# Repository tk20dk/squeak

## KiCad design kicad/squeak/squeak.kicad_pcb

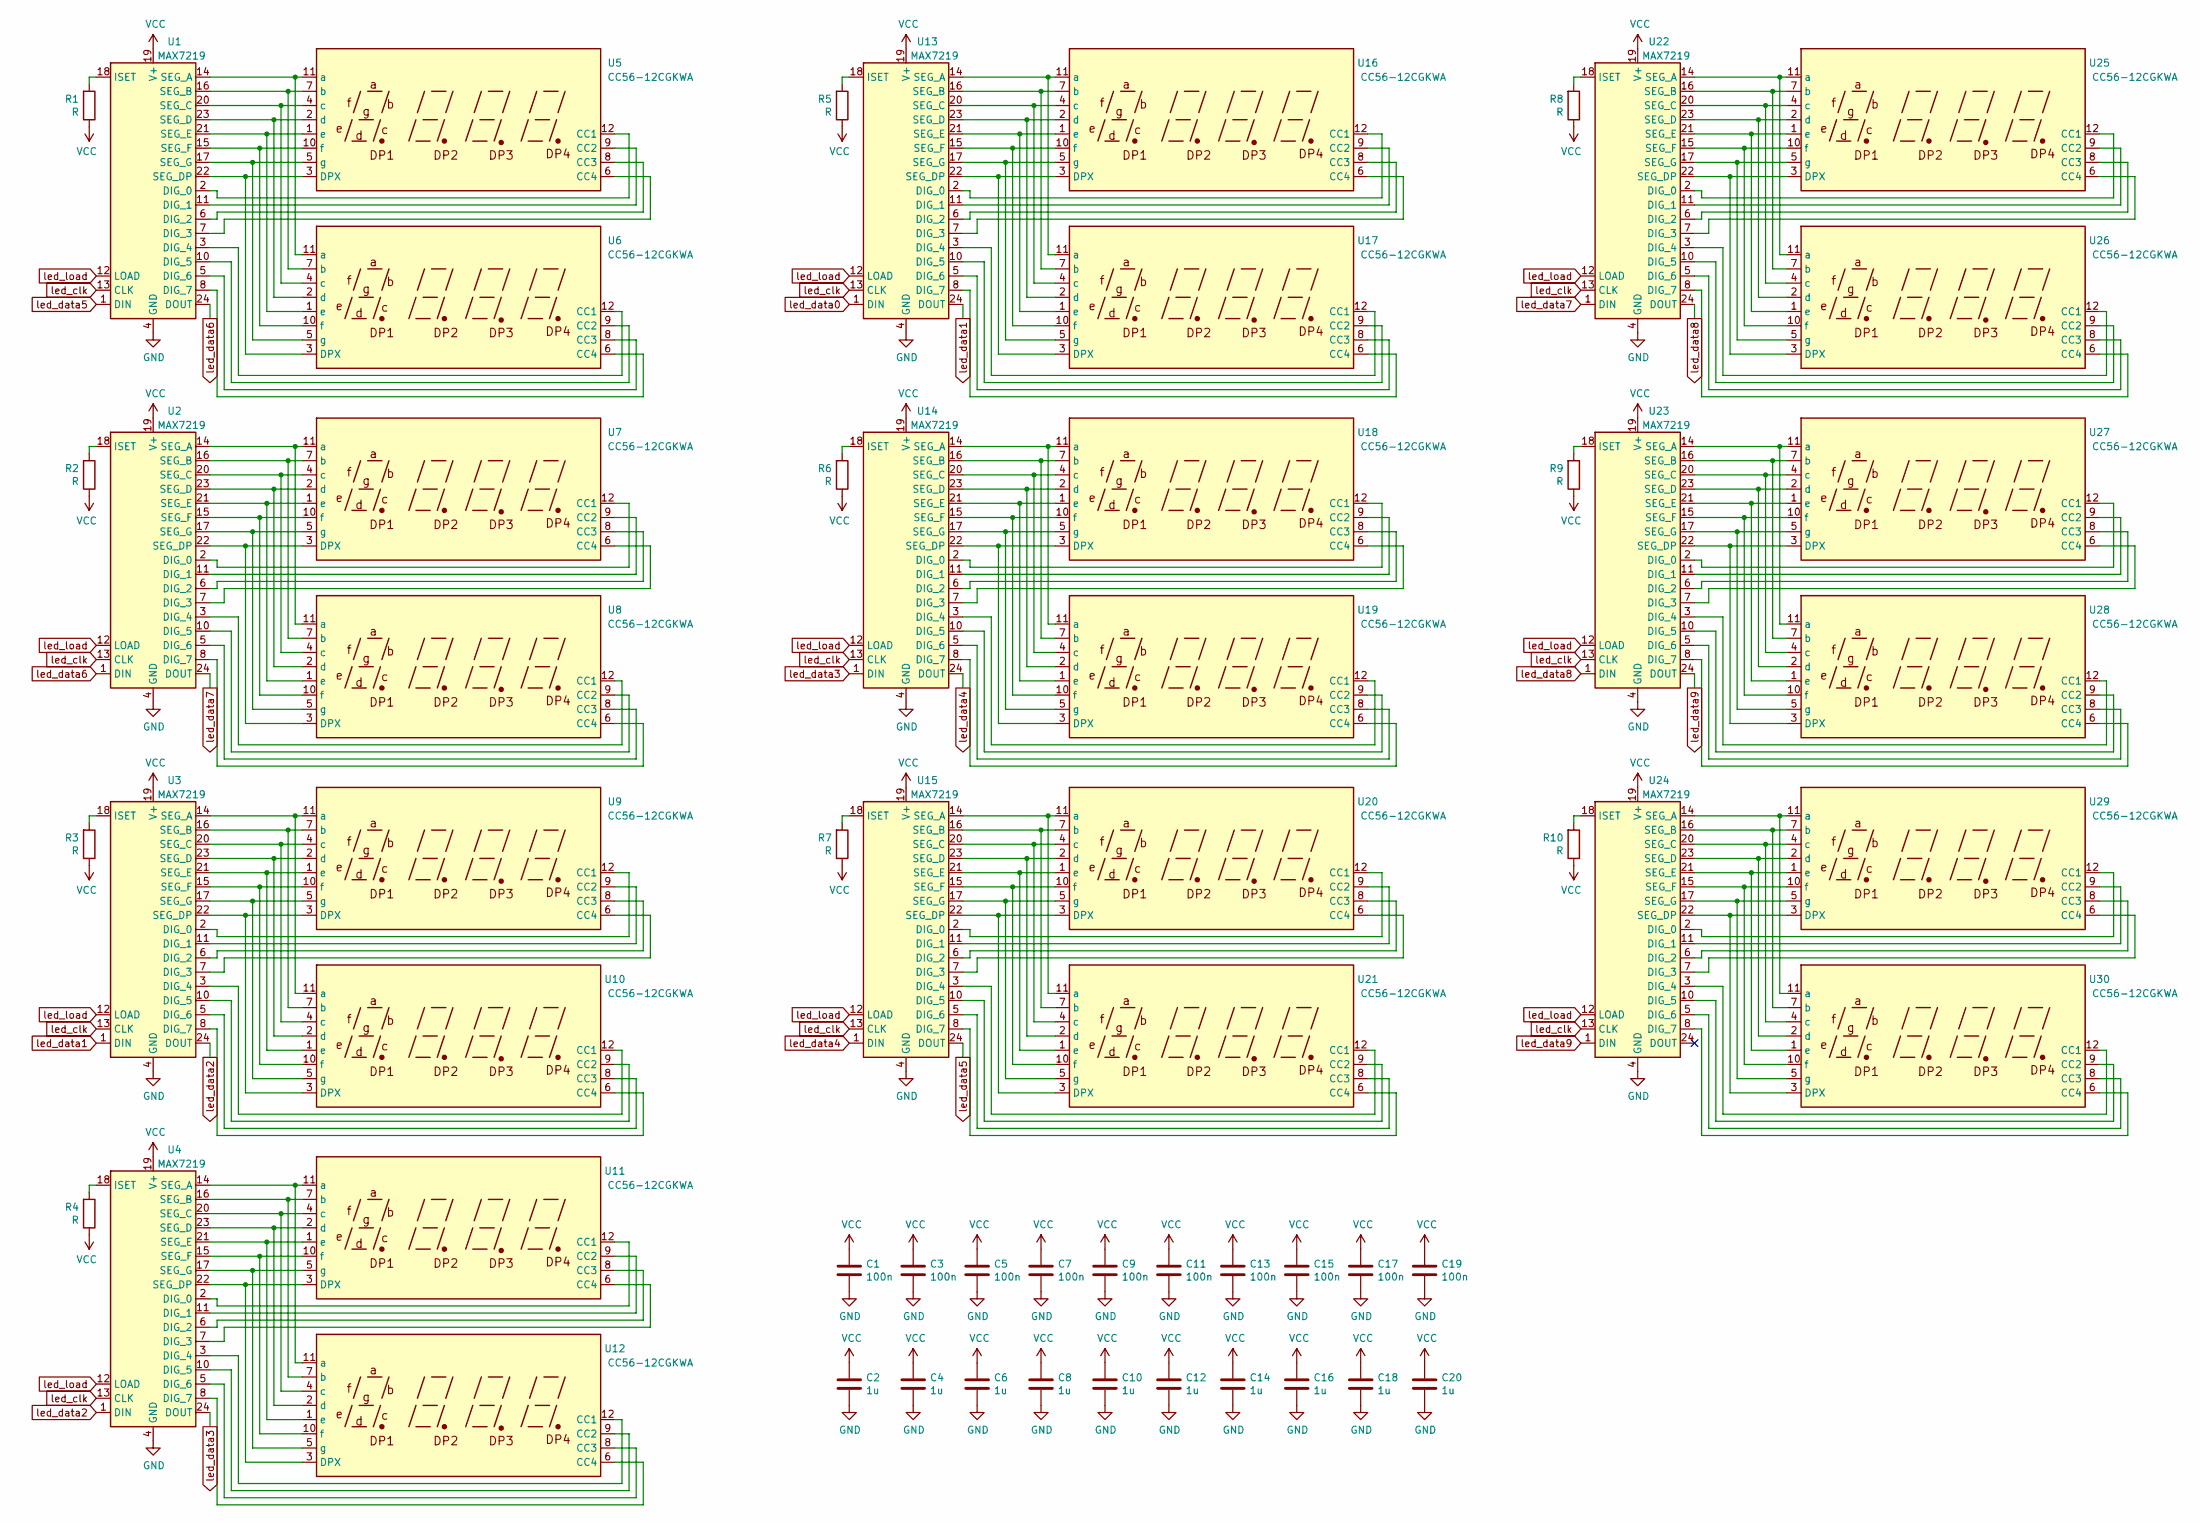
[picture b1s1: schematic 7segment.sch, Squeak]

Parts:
C1, C3, C5, C7, C9, C11, C13, C15, C17, C19: 100n; C_0603_1608Metric
C2, C4, C6, C8, C10, C12, C14, C16, C18, C20: 1u; C_0805_2012Metric
R1, R2, R3, R4, R5, R6, R7, R8, R9, R10: R; R_0603_1608Metric
U1, U2, U3, U4, U13, U14, U15, U22, U23, U24: MAX7219; SOIC-24W_7.5x15.4mm_P1.27mm
U5, U6, U7, U8, U9, U10, U11, U12, U16, U17, U18, U19, U20, U21, U25, U26, U27, U28, U29, U30: CC56-12CGKWA; CA56-12CGKWA

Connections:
GND: C1.2, C2.2, C3.2, C4.2, C5.2, C6.2, C7.2, C8.2, C9.2, C10.2, C11.2, C12.2, C13.2, C14.2, C15.2, C16.2, C17.2, C18.2, C19.2, C20.2, U1.4 (GND), U1.9 (GND), U2.4 (GND), U2.9 (GND), U3.4 (GND), U3.9 (GND), U4.4 (GND), U4.9 (GND), U13.4 (GND), U13.9 (GND), U14.4 (GND), U14.9 (GND), U15.4 (GND), U15.9 (GND), U22.4 (GND), U22.9 (GND), U23.4 (GND), U23.9 (GND), U24.4 (GND), U24.9 (GND); also elsewhere on the board
unnamed: R1.2, U1.18 (ISET)
unnamed: R2.2, U2.18 (ISET)
unnamed: R3.2, U3.18 (ISET)
unnamed: R4.2, U4.18 (ISET)
unnamed: R5.2, U13.18 (ISET)
unnamed: R6.2, U14.18 (ISET)
unnamed: R7.2, U15.18 (ISET)
unnamed: R8.2, U22.18 (ISET)
unnamed: R9.2, U23.18 (ISET)
unnamed: R10.2, U24.18 (ISET)
unnamed: U1.2 (DIG_0), U5.12 (CC1)
unnamed: U1.3 (DIG_4), U6.12 (CC1)
unnamed: U1.5 (DIG_6), U6.8 (CC3)
unnamed: U1.6 (DIG_2), U5.8 (CC3)
unnamed: U1.7 (DIG_3), U5.6 (CC4)
unnamed: U1.8 (DIG_7), U6.6 (CC4)
unnamed: U1.10 (DIG_5), U6.9 (CC2)
unnamed: U1.11 (DIG_1), U5.9 (CC2)
unnamed: U1.14 (SEG_A), U5.11 (a), U6.11 (a)
unnamed: U1.15 (SEG_F), U5.10 (f), U6.10 (f)
unnamed: U1.16 (SEG_B), U5.7 (b), U6.7 (b)
unnamed: U1.17 (SEG_G), U5.5 (g), U6.5 (g)
unnamed: U1.20 (SEG_C), U5.4 (c), U6.4 (c)
unnamed: U1.21 (SEG_E), U5.1 (e), U6.1 (e)
unnamed: U1.22 (SEG_DP), U5.3 (DPX), U6.3 (DPX)
unnamed: U1.23 (SEG_D), U5.2 (d), U6.2 (d)
unnamed: U2.2 (DIG_0), U7.12 (CC1)
unnamed: U2.3 (DIG_4), U8.12 (CC1)
unnamed: U2.5 (DIG_6), U8.8 (CC3)
unnamed: U2.6 (DIG_2), U7.8 (CC3)
unnamed: U2.7 (DIG_3), U7.6 (CC4)
unnamed: U2.8 (DIG_7), U8.6 (CC4)
unnamed: U2.10 (DIG_5), U8.9 (CC2)
unnamed: U2.11 (DIG_1), U7.9 (CC2)
unnamed: U2.14 (SEG_A), U7.11 (a), U8.11 (a)
unnamed: U2.15 (SEG_F), U7.10 (f), U8.10 (f)
unnamed: U2.16 (SEG_B), U7.7 (b), U8.7 (b)
unnamed: U2.17 (SEG_G), U7.5 (g), U8.5 (g)
unnamed: U2.20 (SEG_C), U7.4 (c), U8.4 (c)
unnamed: U2.21 (SEG_E), U7.1 (e), U8.1 (e)
unnamed: U2.22 (SEG_DP), U7.3 (DPX), U8.3 (DPX)
unnamed: U2.23 (SEG_D), U7.2 (d), U8.2 (d)
unnamed: U3.2 (DIG_0), U9.12 (CC1)
unnamed: U3.6 (DIG_2), U9.8 (CC3)
unnamed: U3.7 (DIG_3), U9.6 (CC4)
unnamed: U3.11 (DIG_1), U9.9 (CC2)
unnamed: U3.21 (SEG_E), U9.1 (e), U10.1 (e)
unnamed: U3.23 (SEG_D), U9.2 (d), U10.2 (d)
unnamed: U3.22 (SEG_DP), U9.3 (DPX), U10.3 (DPX)
unnamed: U3.20 (SEG_C), U9.4 (c), U10.4 (c)
unnamed: U3.17 (SEG_G), U9.5 (g), U10.5 (g)
unnamed: U3.8 (DIG_7), U10.6 (CC4)
unnamed: U3.16 (SEG_B), U9.7 (b), U10.7 (b)
unnamed: U3.5 (DIG_6), U10.8 (CC3)
unnamed: U3.10 (DIG_5), U10.9 (CC2)
unnamed: U3.15 (SEG_F), U9.10 (f), U10.10 (f)
unnamed: U3.14 (SEG_A), U9.11 (a), U10.11 (a)
unnamed: U3.3 (DIG_4), U10.12 (CC1)
unnamed: U4.21 (SEG_E), U11.1 (e), U12.1 (e)
unnamed: U4.23 (SEG_D), U11.2 (d), U12.2 (d)
unnamed: U4.22 (SEG_DP), U11.3 (DPX), U12.3 (DPX)
unnamed: U4.20 (SEG_C), U11.4 (c), U12.4 (c)
unnamed: U4.17 (SEG_G), U11.5 (g), U12.5 (g)
unnamed: U4.7 (DIG_3), U11.6 (CC4)
unnamed: U4.16 (SEG_B), U11.7 (b), U12.7 (b)
unnamed: U4.6 (DIG_2), U11.8 (CC3)
unnamed: U4.11 (DIG_1), U11.9 (CC2)
unnamed: U4.15 (SEG_F), U11.10 (f), U12.10 (f)
unnamed: U4.14 (SEG_A), U11.11 (a), U12.11 (a)
unnamed: U4.2 (DIG_0), U11.12 (CC1)
unnamed: U4.8 (DIG_7), U12.6 (CC4)
unnamed: U4.5 (DIG_6), U12.8 (CC3)
unnamed: U4.10 (DIG_5), U12.9 (CC2)
unnamed: U4.3 (DIG_4), U12.12 (CC1)
unnamed: U13.2 (DIG_0), U16.12 (CC1)
unnamed: U13.3 (DIG_4), U17.12 (CC1)
unnamed: U13.5 (DIG_6), U17.8 (CC3)
unnamed: U13.6 (DIG_2), U16.8 (CC3)
unnamed: U13.7 (DIG_3), U16.6 (CC4)
unnamed: U13.8 (DIG_7), U17.6 (CC4)
unnamed: U13.10 (DIG_5), U17.9 (CC2)
unnamed: U13.11 (DIG_1), U16.9 (CC2)
unnamed: U13.14 (SEG_A), U16.11 (a), U17.11 (a)
unnamed: U13.15 (SEG_F), U16.10 (f), U17.10 (f)
unnamed: U13.16 (SEG_B), U16.7 (b), U17.7 (b)
unnamed: U13.17 (SEG_G), U16.5 (g), U17.5 (g)
unnamed: U13.20 (SEG_C), U16.4 (c), U17.4 (c)
unnamed: U13.21 (SEG_E), U16.1 (e), U17.1 (e)
unnamed: U13.22 (SEG_DP), U16.3 (DPX), U17.3 (DPX)
unnamed: U13.23 (SEG_D), U16.2 (d), U17.2 (d)
unnamed: U14.2 (DIG_0), U18.12 (CC1)
unnamed: U14.3 (DIG_4), U19.12 (CC1)
unnamed: U14.5 (DIG_6), U19.8 (CC3)
unnamed: U14.6 (DIG_2), U18.8 (CC3)
unnamed: U14.7 (DIG_3), U18.6 (CC4)
unnamed: U14.8 (DIG_7), U19.6 (CC4)
unnamed: U14.10 (DIG_5), U19.9 (CC2)
unnamed: U14.11 (DIG_1), U18.9 (CC2)
unnamed: U14.14 (SEG_A), U18.11 (a), U19.11 (a)
unnamed: U14.15 (SEG_F), U18.10 (f), U19.10 (f)
unnamed: U14.16 (SEG_B), U18.7 (b), U19.7 (b)
unnamed: U14.17 (SEG_G), U18.5 (g), U19.5 (g)
unnamed: U14.20 (SEG_C), U18.4 (c), U19.4 (c)
unnamed: U14.21 (SEG_E), U18.1 (e), U19.1 (e)
unnamed: U14.22 (SEG_DP), U18.3 (DPX), U19.3 (DPX)
unnamed: U14.23 (SEG_D), U18.2 (d), U19.2 (d)
unnamed: U15.2 (DIG_0), U20.12 (CC1)
unnamed: U15.3 (DIG_4), U21.12 (CC1)
unnamed: U15.5 (DIG_6), U21.8 (CC3)
unnamed: U15.6 (DIG_2), U20.8 (CC3)
unnamed: U15.7 (DIG_3), U20.6 (CC4)
unnamed: U15.8 (DIG_7), U21.6 (CC4)
unnamed: U15.10 (DIG_5), U21.9 (CC2)
unnamed: U15.11 (DIG_1), U20.9 (CC2)
unnamed: U15.14 (SEG_A), U20.11 (a), U21.11 (a)
unnamed: U15.15 (SEG_F), U20.10 (f), U21.10 (f)
unnamed: U15.16 (SEG_B), U20.7 (b), U21.7 (b)
unnamed: U15.17 (SEG_G), U20.5 (g), U21.5 (g)
unnamed: U15.20 (SEG_C), U20.4 (c), U21.4 (c)
unnamed: U15.21 (SEG_E), U20.1 (e), U21.1 (e)
unnamed: U15.22 (SEG_DP), U20.3 (DPX), U21.3 (DPX)
unnamed: U15.23 (SEG_D), U20.2 (d), U21.2 (d)
unnamed: U22.2 (DIG_0), U25.12 (CC1)
unnamed: U22.3 (DIG_4), U26.12 (CC1)
unnamed: U22.5 (DIG_6), U26.8 (CC3)
unnamed: U22.6 (DIG_2), U25.8 (CC3)
unnamed: U22.7 (DIG_3), U25.6 (CC4)
unnamed: U22.8 (DIG_7), U26.6 (CC4)
unnamed: U22.10 (DIG_5), U26.9 (CC2)
unnamed: U22.11 (DIG_1), U25.9 (CC2)
unnamed: U22.14 (SEG_A), U25.11 (a), U26.11 (a)
unnamed: U22.15 (SEG_F), U25.10 (f), U26.10 (f)
unnamed: U22.16 (SEG_B), U25.7 (b), U26.7 (b)
unnamed: U22.17 (SEG_G), U25.5 (g), U26.5 (g)
unnamed: U22.20 (SEG_C), U25.4 (c), U26.4 (c)
unnamed: U22.21 (SEG_E), U25.1 (e), U26.1 (e)
unnamed: U22.22 (SEG_DP), U25.3 (DPX), U26.3 (DPX)
unnamed: U22.23 (SEG_D), U25.2 (d), U26.2 (d)
unnamed: U23.2 (DIG_0), U27.12 (CC1)
unnamed: U23.3 (DIG_4), U28.12 (CC1)
unnamed: U23.5 (DIG_6), U28.8 (CC3)
unnamed: U23.6 (DIG_2), U27.8 (CC3)
unnamed: U23.7 (DIG_3), U27.6 (CC4)
unnamed: U23.8 (DIG_7), U28.6 (CC4)
unnamed: U23.10 (DIG_5), U28.9 (CC2)
unnamed: U23.11 (DIG_1), U27.9 (CC2)
unnamed: U23.14 (SEG_A), U27.11 (a), U28.11 (a)
unnamed: U23.15 (SEG_F), U27.10 (f), U28.10 (f)
unnamed: U23.16 (SEG_B), U27.7 (b), U28.7 (b)
unnamed: U23.17 (SEG_G), U27.5 (g), U28.5 (g)
unnamed: U23.20 (SEG_C), U27.4 (c), U28.4 (c)
unnamed: U23.21 (SEG_E), U27.1 (e), U28.1 (e)
unnamed: U23.22 (SEG_DP), U27.3 (DPX), U28.3 (DPX)
unnamed: U23.23 (SEG_D), U27.2 (d), U28.2 (d)
unnamed: U24.2 (DIG_0), U29.12 (CC1)
unnamed: U24.3 (DIG_4), U30.12 (CC1)
unnamed: U24.5 (DIG_6), U30.8 (CC3)
unnamed: U24.6 (DIG_2), U29.8 (CC3)
unnamed: U24.7 (DIG_3), U29.6 (CC4)
unnamed: U24.8 (DIG_7), U30.6 (CC4)
unnamed: U24.10 (DIG_5), U30.9 (CC2)
unnamed: U24.11 (DIG_1), U29.9 (CC2)
unnamed: U24.14 (SEG_A), U29.11 (a), U30.11 (a)
unnamed: U24.15 (SEG_F), U29.10 (f), U30.10 (f)
unnamed: U24.16 (SEG_B), U29.7 (b), U30.7 (b)
unnamed: U24.17 (SEG_G), U29.5 (g), U30.5 (g)
unnamed: U24.20 (SEG_C), U29.4 (c), U30.4 (c)
unnamed: U24.21 (SEG_E), U29.1 (e), U30.1 (e)
unnamed: U24.22 (SEG_DP), U29.3 (DPX), U30.3 (DPX)
unnamed: U24.23 (SEG_D), U29.2 (d), U30.2 (d)
VCC: C1.1, C2.1, C3.1, C4.1, C5.1, C6.1, C7.1, C8.1, C9.1, C10.1, C11.1, C12.1, C13.1, C14.1, C15.1, C16.1, C17.1, C18.1, C19.1, C20.1, R1.1, R2.1, R3.1, R4.1, R5.1, R6.1, R7.1, R8.1, R9.1, R10.1, U1.19 (V+), U2.19 (V+), U3.19 (V+), U4.19 (V+), U13.19 (V+), U14.19 (V+), U15.19 (V+), U22.19 (V+), U23.19 (V+), U24.19 (V+); also elsewhere on the board
led_clk: U1.13 (CLK), U2.13 (CLK), U3.13 (CLK), U4.13 (CLK), U13.13 (CLK), U14.13 (CLK), U15.13 (CLK), U22.13 (CLK), U23.13 (CLK), U24.13 (CLK); also elsewhere on the board
led_data0: U13.1 (DIN); also elsewhere on the board
led_data1: U3.1 (DIN), U13.24 (DOUT)
led_data2: U3.24 (DOUT), U4.1 (DIN)
led_data3: U4.24 (DOUT), U14.1 (DIN)
led_data4: U14.24 (DOUT), U15.1 (DIN)
led_data5: U1.1 (DIN), U15.24 (DOUT)
led_data6: U1.24 (DOUT), U2.1 (DIN)
led_data7: U2.24 (DOUT), U22.1 (DIN)
led_data8: U22.24 (DOUT), U23.1 (DIN)
led_data9: U23.24 (DOUT), U24.1 (DIN)
led_load: U1.12 (LOAD), U2.12 (LOAD), U3.12 (LOAD), U4.12 (LOAD), U13.12 (LOAD), U14.12 (LOAD), U15.12 (LOAD), U22.12 (LOAD), U23.12 (LOAD), U24.12 (LOAD); also elsewhere on the board

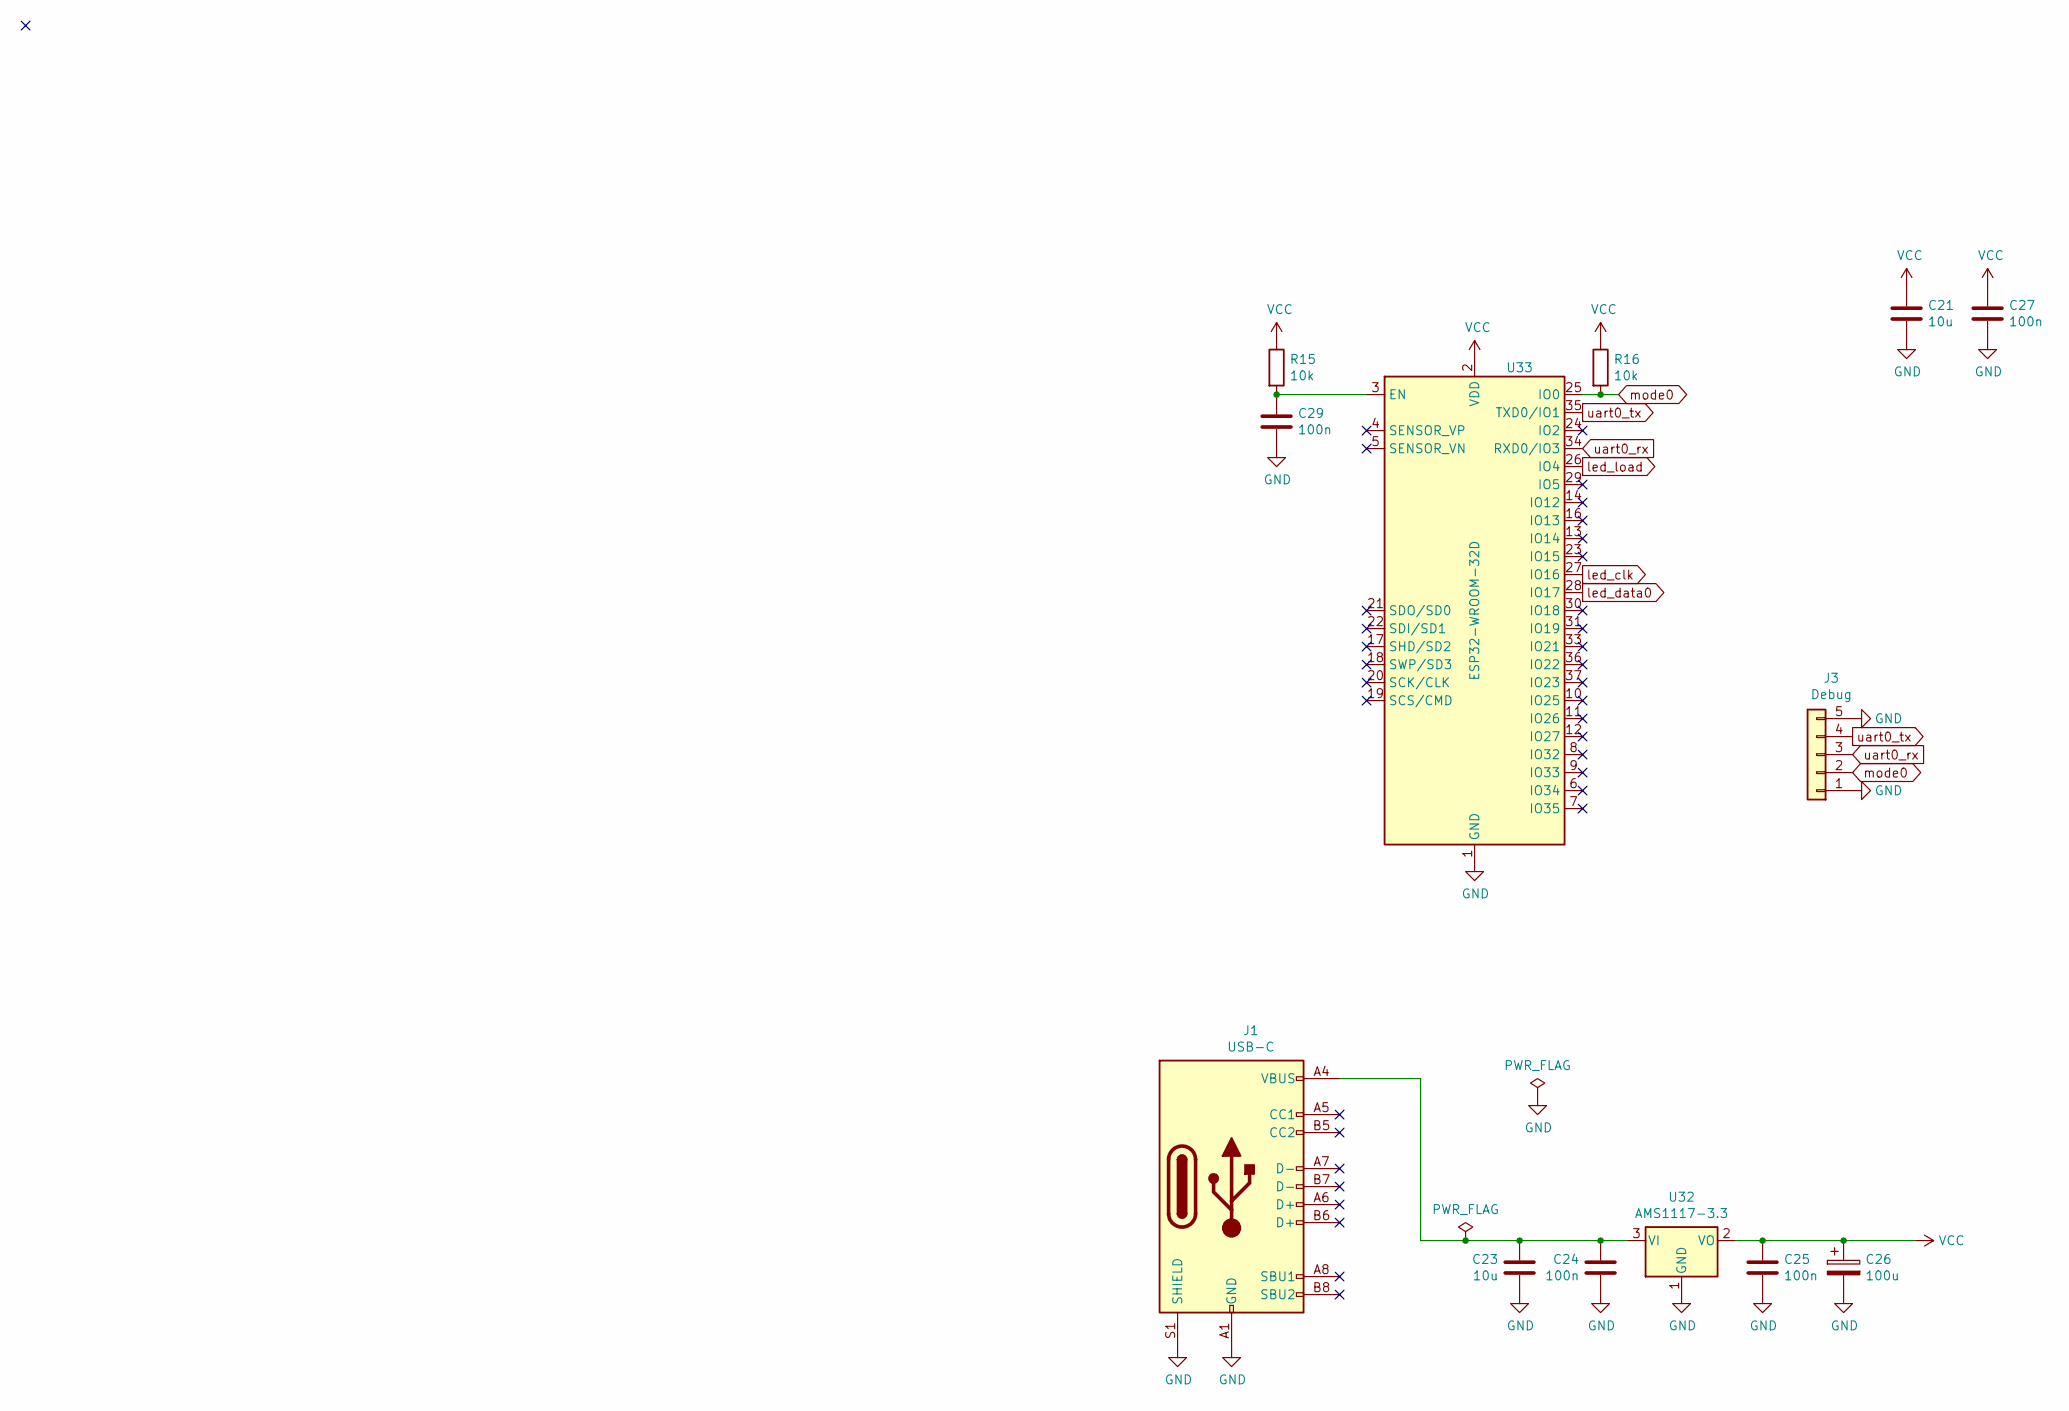
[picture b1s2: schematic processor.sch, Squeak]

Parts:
C21, C23: 10u; C_1206_3216Metric
C24, C25, C27, C29: 100n; C_0603_1608Metric
C26: 100u; CP_EIA-3528-12_Kemet-T
J1: USB-C; USB_C_Receptacle_XKB_U262-16XN-4BVC11
J3: Debug; PinHeader_1x05_P2.54mm_Vertical
R15, R16: 10k; R_0603_1608Metric
U32: AMS1117-3.3; SOT-223-3_TabPin2
U33: ESP32-WROOM-32D; ESP32-WROOM-32

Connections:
GND: C21.2, C23.1, C24.1, C25.2, C26.2, C27.2, C29.2, J1.A1 (GND), J1.A12 (GND), J1.B1 (GND), J1.B12 (GND), J1.S1 (SHIELD), J3.1, J3.5, U32.1 (GND), U33.1 (GND), U33.15 (GND), U33.38 (GND), U33.39 (GND); also elsewhere on the board
unnamed: C23.2, C24.2, J1.A4 (VBUS), J1.A9 (VBUS), J1.B4 (VBUS), J1.B9 (VBUS), U32.3 (VI)
unnamed: C29.1, R15.2, U33.3 (EN)
VCC: C21.1, C25.1, C26.1, C27.1, R15.1, R16.1, U32.2 (VO), U33.2 (VDD); also elsewhere on the board
led_clk: U33.27 (IO16); also elsewhere on the board
led_data0: U33.28 (IO17); also elsewhere on the board
led_load: U33.26 (IO4); also elsewhere on the board
mode0: J3.2, R16.2, U33.25 (IO0)
uart0_rx: J3.3, U33.34 (RXD0/IO3)
uart0_tx: J3.4, U33.35 (TXD0/IO1)

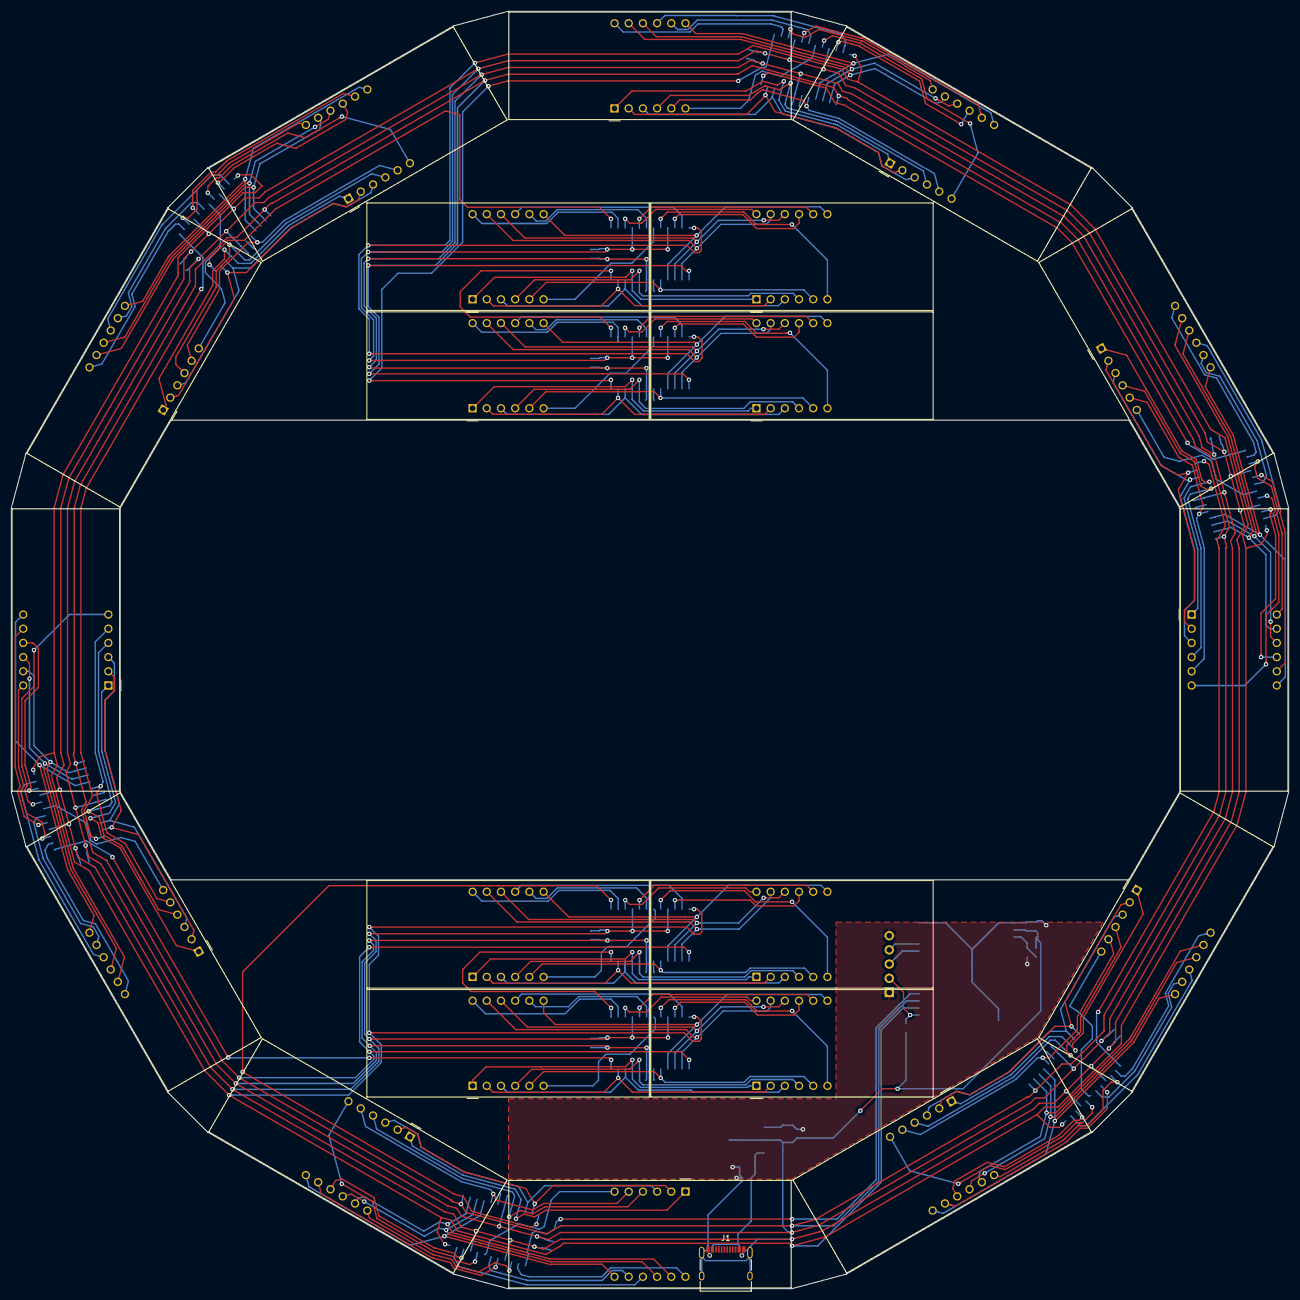
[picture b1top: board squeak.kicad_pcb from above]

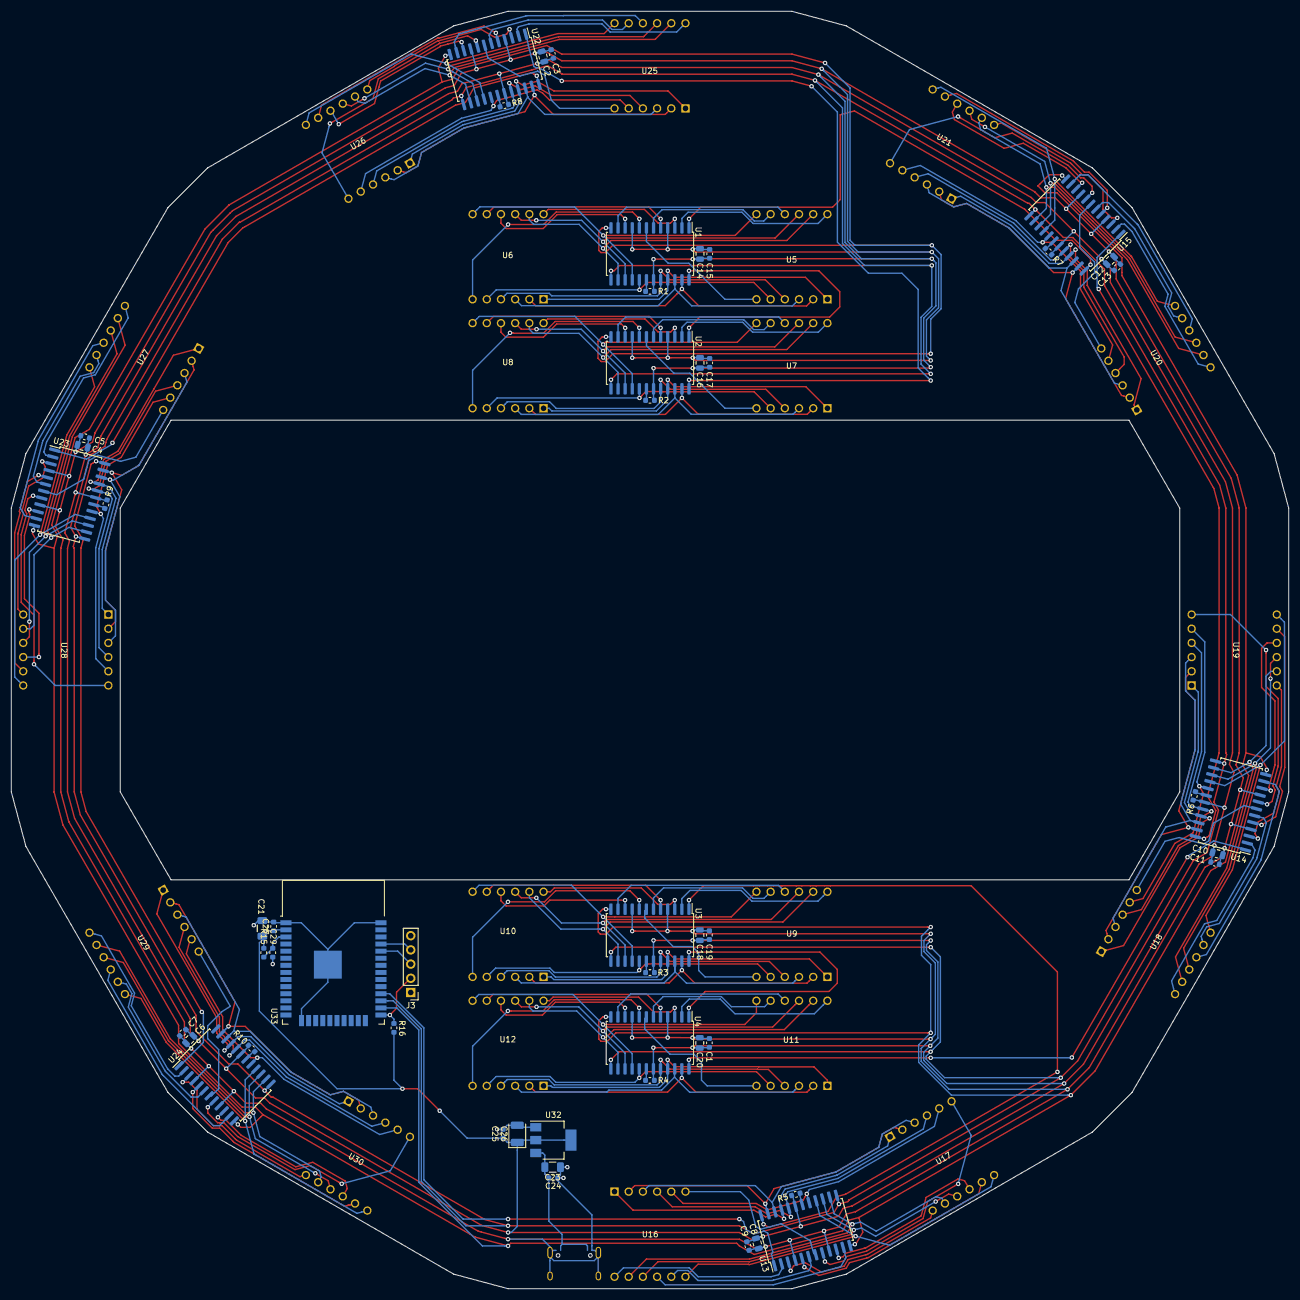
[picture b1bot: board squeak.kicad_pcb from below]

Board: 2 copper layers, 228.6 x 228.6 mm, 73 parts (52 on the bottom side), 189 nets.

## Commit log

2020-11-20 created initial kicad project
